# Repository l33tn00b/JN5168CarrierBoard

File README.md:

# JN5168CarrierBoard
Carrier Board for JN5168 Module with Reset and Programming Button; Step-Down Regulator (24V DC input).

This is a carrier board for JN5168 ZigBee modules. All pins are broken out. Reset and Programming buttons are provided. The better part of the carrier module is occupied by parts for the step-down voltage regulator. Reverse input polarity protection is provided (except for the input buffer capacitor, if placed). 

Above stated imput voltage limit (24V) depends on the FET used for polarity protection and the voltage rating of the input buffer capacitor. The chosen FET for polarity protection is rated for up to 30V. Omitting or replacing this FET and placing an appropriate buffer capacitor allow for input voltages up to the limit of the DC-DC step-down regulator, i.e. 45V.

Voltage is supplied via RIACON Connectors (screw terminals that may be pulled off from their pins).

Here is a representation created by KiCAD:

This is the schematic:

There you go, a real PCB (to the left):

On the above picture you might realize the voltage supply (red and black) is done via clamps instead of the screw terminal: This is due to the RIACON screw terminal that can just be pulled off the solder pins.

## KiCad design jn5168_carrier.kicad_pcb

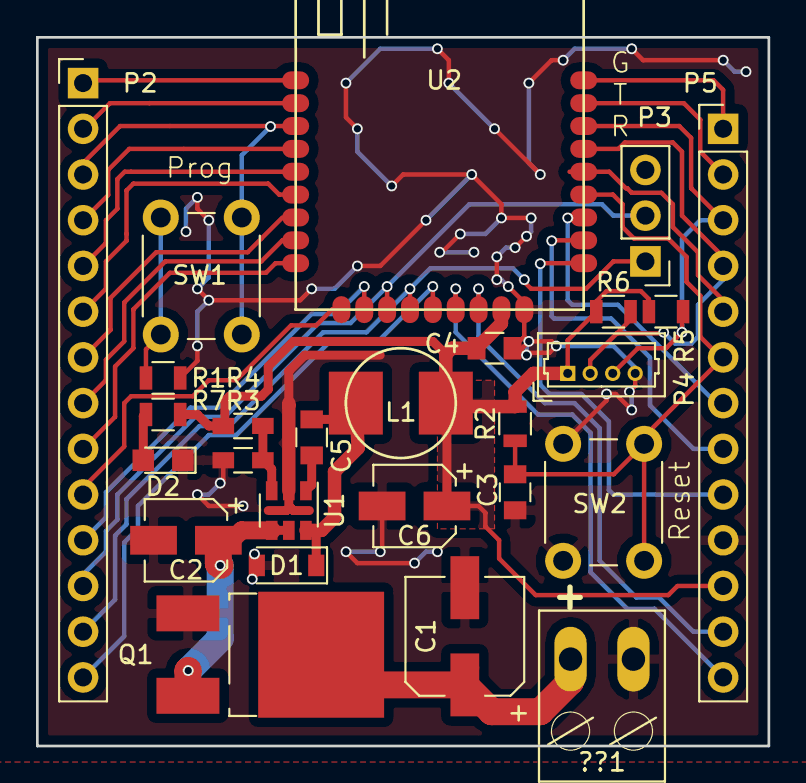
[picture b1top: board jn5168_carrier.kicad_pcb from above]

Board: 2 copper layers, 40.6 x 39.4 mm, 26 parts (0 on the bottom side), 34 nets.

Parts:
??1: RIACON-2; con-riacon-RIACON-2
C1: 100u; CP_Elec_6.3x7.7
C2: 2u2; CP_Elec_4x5.8
C3: 470n; C_0805
C4: 100n; C_0805
C5: 0.15u .. 1u; C_0805
C6: 10u; CP_Elec_4x5.8
D1: PMEG4010ETR; D_SOD-123
D2: LED; LED_0805
L1: 15u; Murata_LQH55D
P2: CONN_01X14; Pin_Header_Straight_1x14_Pitch2.54mm
P3: SerConn; Pin_Header_Straight_1x03_Pitch2.54mm
P4: I2CConn; Molex_PicoBlade_53047-0410_04x1.25mm_Straight
P5: CONN_01X13; Pin_Header_Straight_1x13_Pitch2.54mm
Q1: AO417; TO-252-2Lead
R1: 10k; R_0805
R2: 18k; R_0805
R3: 1.02k; R_0603_HandSoldering
R4: 3.4k; R_0603_HandSoldering
R5, R6: 4k7; R_0805
R7: 750; R_0805
SW1: Prog; SW_PUSH_6mm
SW2: Reset; SW_PUSH_6mm
U1: LM2840; SOT-23-6
U2: JN5168-001-M00

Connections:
+3V3: C4.1, C6.1, L1.2, P4.1, P5.11, R2.1, R4.1, R5.1, R6.1, R7.1, U2.17
/ADC1: P2.1, U2.1
/ADC2: P5.1, U2.27
/DIO0: P2.6, U2.6
/DIO1: P2.7, U2.7
/DIO2: P2.8, U2.8
/DIO3: P2.9, U2.9
/DIO4: P2.10, U2.10
/DIO5: P2.11, U2.11
/DIO6TX: P2.12, P3.2, U2.12
/DIO7RX: P2.13, P3.1, U2.13
/DIO8: P2.14, U2.14
/DIO9: P5.13, U2.15
/DIO15SDA: P4.2, P5.4, R6.2, U2.24
/DIO16SCL: P4.3, P5.3, R5.2, U2.25
/DIO17: P5.2, U2.26
/MISO: P2.3, SW1.2, U2.3
/MOSI: P2.4, U2.4
/PWM0: P5.12, U2.16
/PWM1: P5.9, U2.19
/PWM2: P5.8, U2.20
/PWM3: P5.7, U2.21
/PWM4: P5.5, U2.23
/RESET: C3.1, P5.6, R2.2, SW2.2, U2.22
/SPICLK: P2.2, U2.2
/SSZ: P2.5, U2.5
GND: ??1.P$2, C1.2, C2.2, C3.2, C4.2, C6.2, D1.2, D2.1, P3.3, P4.4, P5.10, Q1.1, R1.2, R3.2, SW2.1, U1.2, U2.18
unnamed: C2.1, Q1.3, U1.4, U1.5
unnamed: C5.1, D1.1, L1.1, U1.6
unnamed: C5.2, U1.1
unnamed: D2.2, R7.2
unnamed: R1.1, SW1.1
unnamed: R3.1, R4.2, U1.3
VCC: ??1.P$1, C1.1, Q1.2
